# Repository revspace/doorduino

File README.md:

# Doorduino

## Configuration

Create a configuration file for every door, in which 'dev' points to the
serial device of the associated Arduino. The configuration file has to be valid
Perl syntax, and return a list of key/value pairs.

    echo "dev => '/dev/ttyUSB0'" > /home/pi/frontdoor.conf.pl
    echo "dev => '/dev/ttyUSB1'" > /home/pi/backdoor.conf.pl

Add keys to files in `ibuttons.acl.d`, and optionally add executable scripts to
`granted.d` and `denied.d`.

An example configuration file:

    dev => "/dev/ttyUSB0",
    ircname => "main door",
    allow_insecure => 1,

Valid configuration entries are:

| Key              | Default value    | Description
| ---------------- | ---------------- | -------------
| `dev`            | (mandatory)      | Arduino serial device
| `ircname`        | (config name)    | Display name
| `acldir`         | `ibuttons.acl.d` | Directory in which to look for .acl files
| `allow_insecure` | 0                | Set to a true value (such as 1) to enable ID-only access 

## ID-only support (insecure mode)

By default, only SHA1 secure iButtons (DS1961S) are supported. Some
organizations will have insecure ID-only iButtons (like the DS1990A), and want
to upgrade. In other cases, leaking the shared secret would be worse than
allowing access to the wrong people, and you may want to authenticate against
the ID without having the secret available on the controlling Linux computer
(e.g. Raspberry Pi) if you fear the physical controlling device might get
stolen or broken into.

In these cases, set `allow_insecure => 1`. Note that if there's a secret in the
.acl file, it will still be verified. To disable SHA1 verification of the
shared secret, list the ID without a colon or a secret.

## Starting manually, in the foreground

    ./doorduino.pl frontdoor  # or another config file

## Starting automatically using the systemd unit

    cp doorduino@.service /etc/systemd/system

    systemctl enable doorduino@frontdoor
    systemctl enable doorduino@backdoor

    systemctl status doorduino@frontdoor

## Starting automatically with cron

See `doc/crontab.example` and `scripts/restartloop.sh`

## See also

https://revspace.nl/Doorduino

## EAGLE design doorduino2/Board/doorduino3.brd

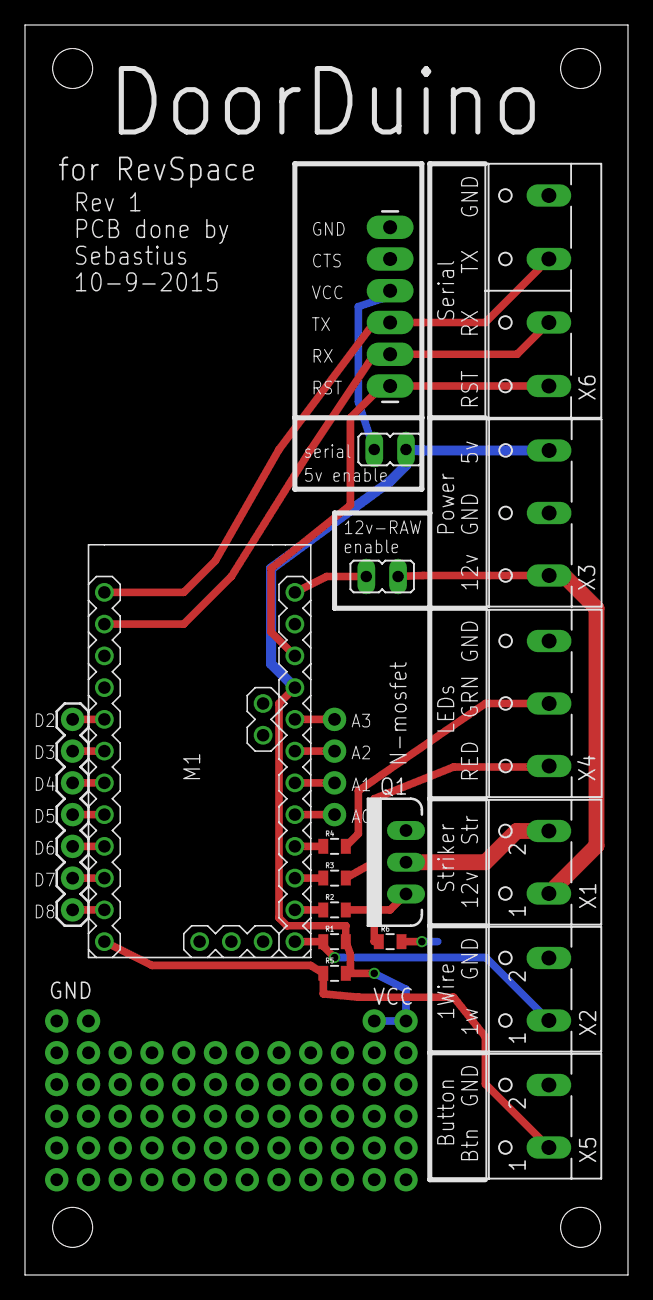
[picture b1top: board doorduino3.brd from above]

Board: 2 copper layers, 48.2 x 100.0 mm, 26 parts (0 on the bottom side), 28 nets.

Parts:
GND: 1X02_NO_SILK
JP1, JP3: JP1
JP2: SERIAL; 1X06_LONGPADS
JP4, JP5, JP6, JP7, JP8: 1X12_NO_SILK
JP10: 1X07
JP11: 1X04_NO_SILK_ALL_ROUND
M1: ARDUINO-PRO-MINI-5.0V#NP; ARDUINO-PRO-MINI#NP
Q1: N-Mosfet; TO220V
R1, R2, R3, R4, R5, R6: 0805
VCC: 1X02_NO_SILK
X1: STRIKER; W237-102
X2: 1WIRE; W237-102
X3: Power; W237-103
X4: LEDS; W237-103
X5: BUTTON; W237-102
X6: W237-4P

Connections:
+12V: JP1.1, X1.1, X3.1
GND: GND.1, GND.2, JP2.5, JP2.6, M1.J3.1, M1.J6.2, M1.J7.9, Q1.3, R6.2, X2.2, X3.2, X4.3, X5.2, X6.4
unnamed: JP1.2, M1.J6.1
unnamed: M1.J6.12, R1.1, X2.1
unnamed: M1.J6.11, R2.1
unnamed: Q1.1, R2.2, R6.1
unnamed: Q1.2, X1.2
unnamed: M1.J6.10, R3.1
unnamed: M1.J6.9, R4.1
unnamed: R3.2, X4.1
unnamed: R4.2, X4.2
unnamed: M1.J7.1, R5.1, X5.1
unnamed: JP2.3, M1.J7.12, X6.3
unnamed: JP2.2, M1.J7.11, X6.2
unnamed: JP2.4, JP3.1
unnamed: JP2.1, M1.J6.3, X6.1
unnamed: JP10.1, M1.J7.2
unnamed: JP10.2, M1.J7.3
unnamed: JP10.3, M1.J7.4
unnamed: JP10.4, M1.J7.5
unnamed: JP10.5, M1.J7.6
unnamed: JP10.6, M1.J7.7
unnamed: JP10.7, M1.J7.8
unnamed: JP11.1, M1.J6.5
unnamed: JP11.2, M1.J6.6
unnamed: JP11.3, M1.J6.7
unnamed: JP11.4, M1.J6.8
VCC: JP3.2, M1.J6.4, R1.2, R5.2, VCC.1, VCC.2, X3.3

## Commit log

2012-10-31 Eerste commit, zoals het nu in productie draait.
2012-10-31 Schematic
2012-10-31 Niet via terminal
2012-11-02 Blijkbaar sloop je een arduino als je die diode niet gebruikt :)
2012-11-15 Configureerbare naam
2013-04-14 Add syslog logging
2013-04-14 Add doorduino-f18-img-howto + scripts
2013-04-28 Meerdere doorduino's per raspi.
2013-04-29 Scriptje om vanaf 'n centrale plek acl's te pushen :)
2013-04-30 restartloop.sh: mv restartloop.sh to the scripts dir
    The updated version was accidentally placed in the repository root,
    fix this up.
2013-04-30 watchdog-ping.sh: Wait for network to come up before starting the watchdog
2013-05-09 Pinout voordeur-doorduino en UTP-kabels
2013-08-17 SHA1 support. For now, still allows keys without a secret.
2013-08-17 SHA1-support (ds1961 library provided by Bertrik)
    Serial speed bumped to increase chance of working challenge/response.
2013-08-17 Workaround for unexpected calculation in Perl/ARM.
2013-08-20 Sneller!
2014-02-10 Secrets in iButtons
2014-11-16 Sparkshack-gl-inet doesn't do syslog yet
2014-11-16 Keepalive - when communication fails, blink red
2015-06-25 Reorg tree for inotool usage. Add OneWire lib files
2015-06-25 Move libraries to lib folder for inotool/arduino compatibility
2015-06-25 2 Way keepalive
2015-10-01 Resistors, mosfet
2015-10-28 Boardlayouts DD3 rev 1
    Boardfiles in Cadsoft Eagle. Deze versie is degene die we nu in huis
    hebben.
2016-06-02 Move restartloop.sh back to root
    This is the script that actually runs the "daemon" in the foreground.
    Having it in the base directory is useful, because that will typically
    be the working directory.
    Maybe at some point we can turn it into a nice systemd unit. But for
    now, screen with a shell loop will do :-)
2016-06-02 Don't log keepalives
    They fill up the log files.
2016-06-02 Add shebang
2016-06-02 Fix test for empty command line argument
2016-06-02 Move files
2016-06-02 Add example acl
2016-06-02 Update push.sh with current version
    Now includes a hack to add someone to a list that isn't
    used with the front door (10.42.42.42).
2016-06-02 Move another file to doc/
2016-06-03 Implement secondary challenge with modified EEPROM
    https://revspace.nl/SecureIButton#Idee_voor_betere_challenge (Dutch)
2016-06-03 Randomly spread EEPROM writes over all data pages
    On interpreting datasheets:
    "MP[7:3] = 01000b, MP[2:0] = T7:T5" just means "0x40 | page_number".
2016-06-03 Rename variable; led off during ibutton comms
    The variable name 'addr' became confusing because the EEPROM also
    uses addresses. The DS1961S datasheet calls them "registration
    numbers", the DS1991 datasheet uses "64-bit ROM code". But 'id'
    is much shorter :-)
2016-06-03 Faster communication to reduce required contact time
2016-06-04 For bouncing contacts, flash green, not yellow
    Users experienced the yellow flash as key rejection (in part because the actual
    color is close to red), while it was intended as an error message, with an
    invitation to try again.
2016-06-21 Reverse logic: start by name, read dev from config
    Old: ./doorduino.pl /dev/ttyUSB0 # reads name from ircname.ttyUSB0
    New: ./doorduino.pl name # reads dev from name.conf.pl
2016-06-21 Remove .conf.pl from name
2016-06-21 systemd unit
2016-06-22 Be chatty on stdout/stderr only on terminals
2016-06-22 Debounce button
2016-06-22 Rev 1.1, mainly cosmetic
    Ground plane on both sides
    Better text size/alignment
    Arduino pinout simplified (less holes!)
    Minor cosmetics
2016-06-22 Folder rename
    DD2 -> DD3
2016-06-26 Script for flashing to ALL connected arduinos
2016-07-11 Spul weg dat niet meer op de space is.
2017-02-14 Add LICENSE
2018-07-25 Fix compilation problems due to missing entropy lib
2018-07-25 Lowercase hex string output
2018-11-28 Add libraries required for building mksecret.ino
2019-01-20 Enable laziness: /home/pi$ git clone .../doorduino
2019-01-20 . is no longer in @INC in newer perls, but it's the only one we wanted :D
2019-02-14 Configurable acl directory (enables per-door acl)
2019-02-14 Script hooks in granted.d and denied.d, instead of hardcoded barsay
2019-02-14 Instructions for script hook directories
2019-02-14 Update documentation
2019-02-14 Reorganize, move arduino stuff to arduino/
2019-02-14 Update color, remove duplicate files
2019-03-06 Allow more comm failures before backoff
2019-03-06 Fix undef warning
2019-03-07 Disable insecure ibuttons by default
    To make sure you don't accidentally forget an iButton's secret, which
    would enable access based on the ID only.
2019-03-07 ACL: Allow only horizontal whitespace between id and name
    It would eat whatever was on the following line :)
2019-10-09 Implement "skip_access" to allow delayed unlocks
2019-10-09 Implement retries for initial challenge
    Mitigates the issue with bouncing contacts
2020-06-01 New feature: external access validation scripts
2023-05-13 platformio.ini

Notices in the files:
parts and their libraries:
SparkFun-DiscreteSemi: Licensing: Creative Commons ShareAlike 4.0 International - https://creativecommons.org/licenses/by-sa/4.0
diy-modules: Released under the Creative Commons Attribution 4.0 International License: http://creativecommons.org/licenses/by/4.0
